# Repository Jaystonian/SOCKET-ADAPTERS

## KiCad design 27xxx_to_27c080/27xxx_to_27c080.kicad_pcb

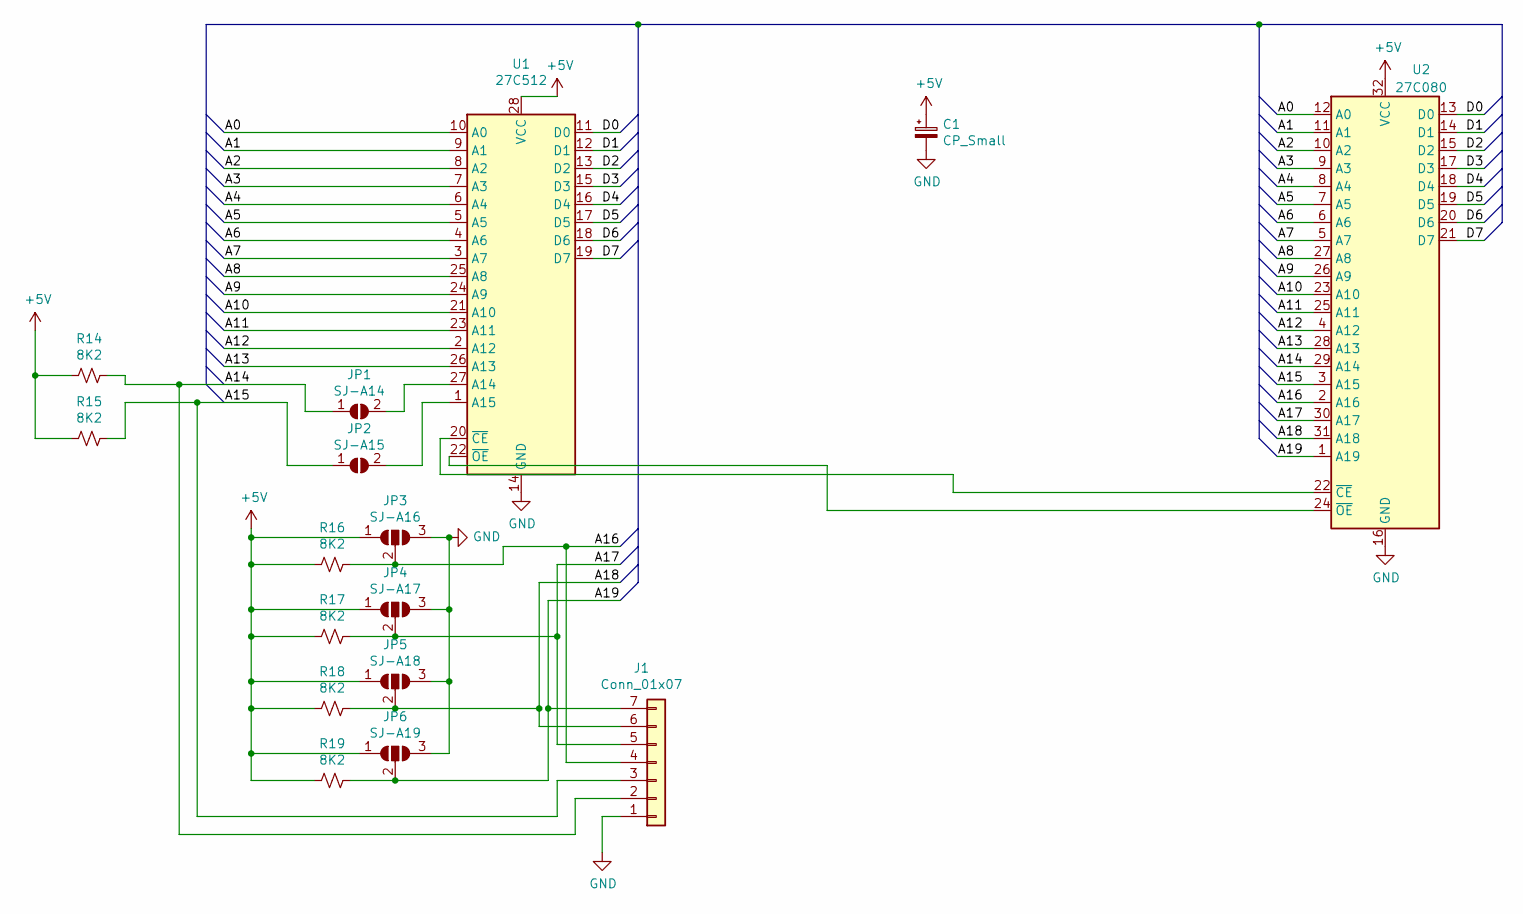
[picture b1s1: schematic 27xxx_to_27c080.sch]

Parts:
C1: CP_Small; CP_EIA-6032-28_Kemet-C_Pad2.25x2.35mm_HandSolder
J1: Conn_01x07; PinHeader_1x07_P2.54mm_Vertical
JP1: SJ-A14; SolderJumper-2_P1.3mm_Open_RoundedPad1.0x1.5mm
JP2: SJ-A15; SolderJumper-2_P1.3mm_Open_RoundedPad1.0x1.5mm
JP3: SJ-A16; SolderJumper-3_P1.3mm_Open_RoundedPad1.0x1.5mm_NumberLabels
JP4: SJ-A17; SolderJumper-3_P1.3mm_Open_RoundedPad1.0x1.5mm_NumberLabels
JP5: SJ-A18; SolderJumper-3_P1.3mm_Open_RoundedPad1.0x1.5mm_NumberLabels
JP6: SJ-A19; SolderJumper-3_P1.3mm_Open_RoundedPad1.0x1.5mm_NumberLabels
R14, R15, R16, R17, R18, R19: 8K2; R_0805_2012Metric_Pad1.15x1.40mm_HandSolder
U1: 27C512; DIP-28_W15.24mm
U2: 27C080; DIP-32_W15.24mm

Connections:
+5V: C1.1, JP3.1 (A), JP4.1 (A), JP5.1 (A), JP6.1 (A), R14.2, R15.2, R16.2, R17.2, R18.2, R19.2, U1.28 (VCC), U2.32 (VCC)
/A0: U1.10 (A0), U2.12 (A0)
/A1: U1.9 (A1), U2.11 (A1)
/A2: U1.8 (A2), U2.10 (A2)
/A3: U1.7 (A3), U2.9 (A3)
/A4: U1.6 (A4), U2.8 (A4)
/A5: U1.5 (A5), U2.7 (A5)
/A6: U1.4 (A6), U2.6 (A6)
/A7: U1.3 (A7), U2.5 (A7)
/A8: U1.25 (A8), U2.27 (A8)
/A9: U1.24 (A9), U2.26 (A9)
/A10: U1.21 (A10), U2.23 (A10)
/A11: U1.23 (A11), U2.25 (A11)
/A12: U1.2 (A12), U2.4 (A12)
/A13: U1.26 (A13), U2.28 (A13)
/A14: J1.2, JP1.1 (A), R14.1, U2.29 (A14)
/A15: J1.3, JP2.1 (A), R15.1, U2.3 (A15)
/A16: J1.4, JP3.2 (C), R16.1, U2.2 (A16)
/A17: J1.5, JP4.2 (C), R17.1, U2.30 (A17)
/A18: J1.6, JP5.2 (C), R18.1, U2.31 (A18)
/A19: J1.7, JP6.2 (C), R19.1, U2.1 (A19)
/D0: U1.11 (D0), U2.13 (D0)
/D1: U1.12 (D1), U2.14 (D1)
/D2: U1.13 (D2), U2.15 (D2)
/D3: U1.15 (D3), U2.17 (D3)
/D4: U1.16 (D4), U2.18 (D4)
/D5: U1.17 (D5), U2.19 (D5)
/D6: U1.18 (D6), U2.20 (D6)
/D7: U1.19 (D7), U2.21 (D7)
GND: C1.2, J1.1, JP3.3 (B), JP4.3 (B), JP5.3 (B), JP6.3 (B), U1.14 (GND), U2.16 (GND)
unnamed: JP1.2 (B), U1.27 (A14)
unnamed: JP2.2 (B), U1.1 (A15)
unnamed: U1.20 (~CE), U2.22 (~CE)
unnamed: U1.22 (~OE), U2.24 (~OE)

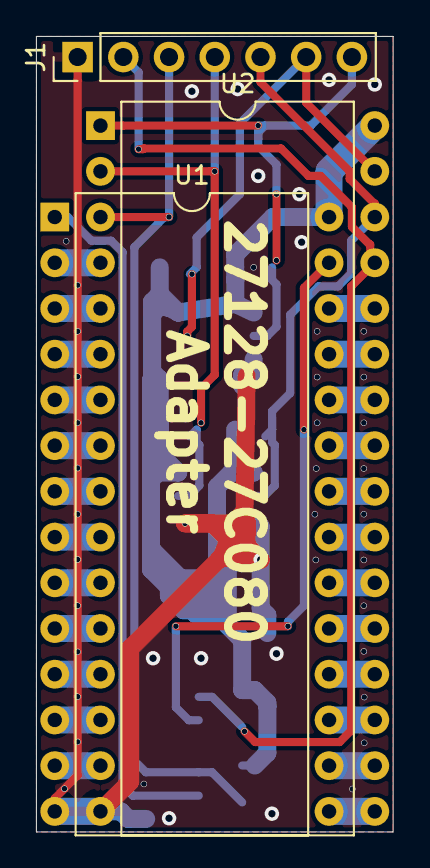
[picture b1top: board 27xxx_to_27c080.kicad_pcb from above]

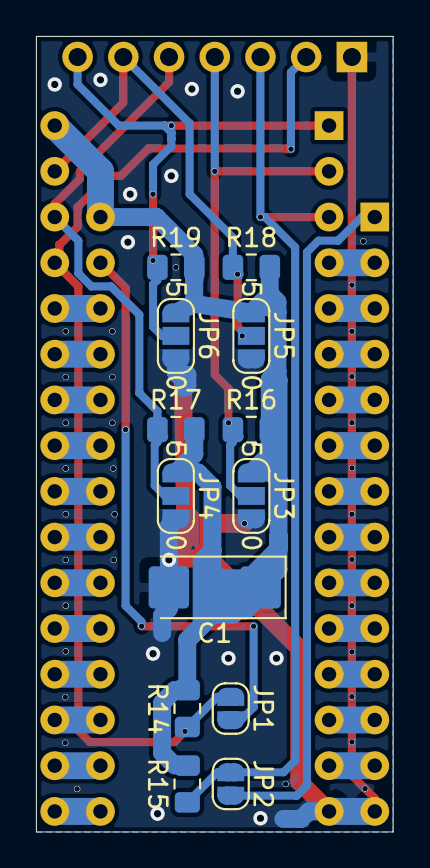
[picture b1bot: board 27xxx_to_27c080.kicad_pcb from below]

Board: 2 copper layers, 19.8 x 44.2 mm, 16 parts (13 on the bottom side), 34 nets.

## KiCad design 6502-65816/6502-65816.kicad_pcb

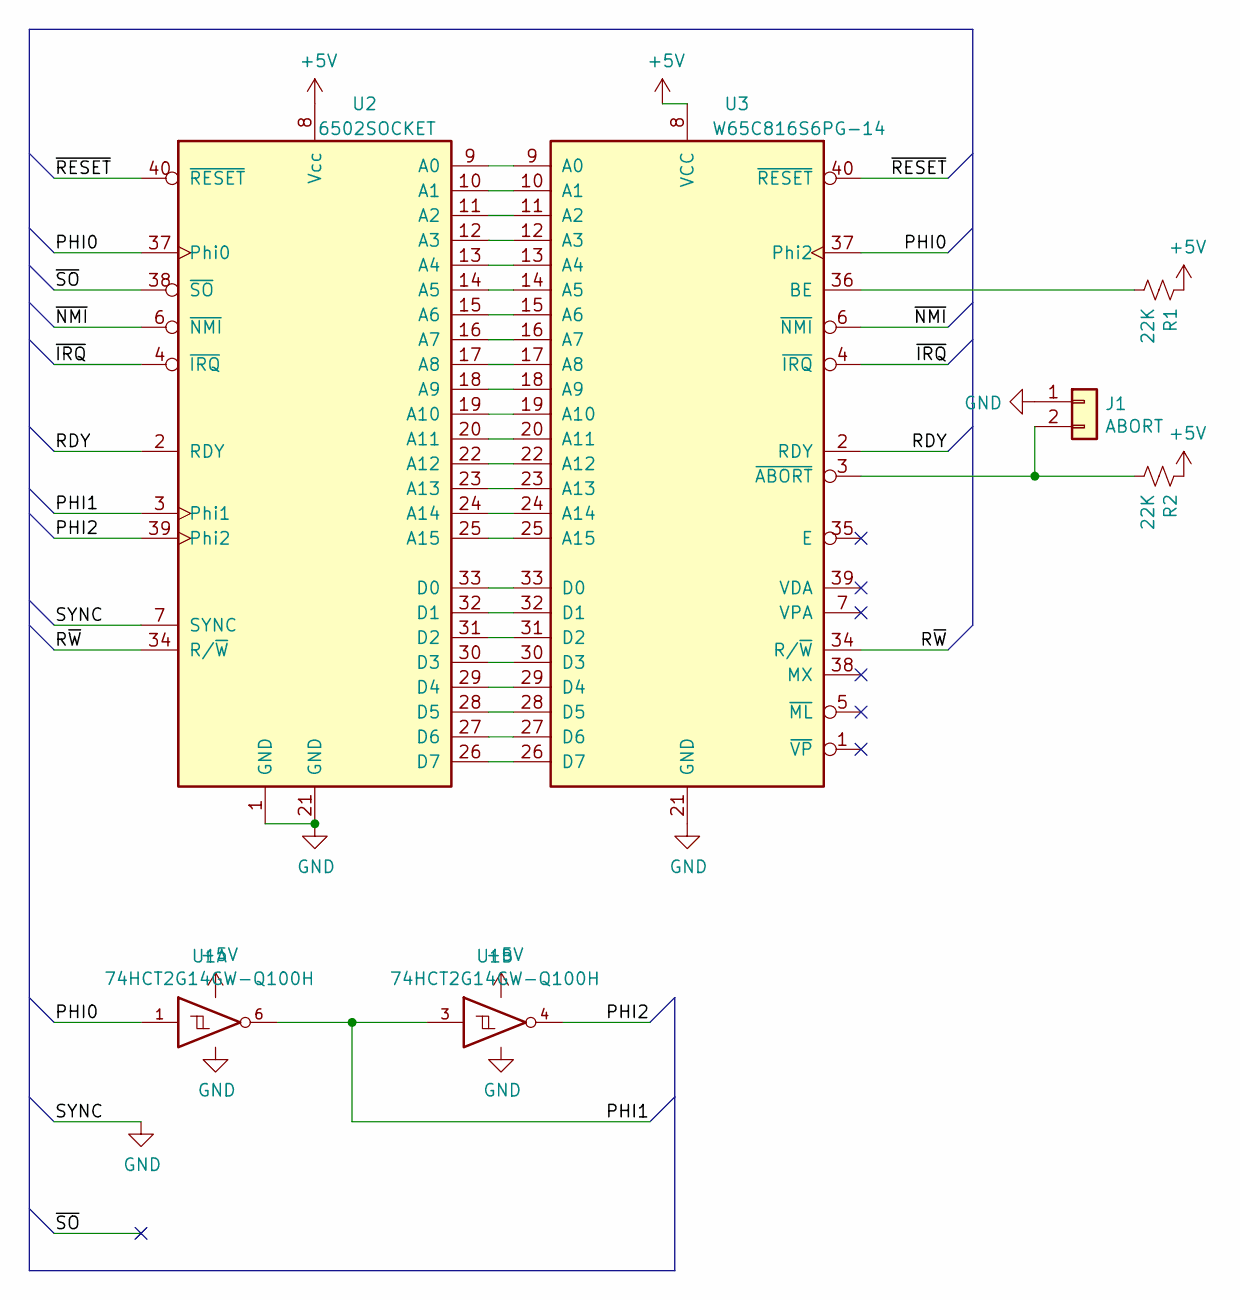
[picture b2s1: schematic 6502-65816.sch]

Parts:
J1: ABORT; PinHeader_1x02_P2.54mm_Vertical
R1, R2: 22K; R_0805_2012Metric_Pad1.15x1.40mm_HandSolder
U1: 74HCT2G14GW-Q100H; TSOP-6_1.65x3.05mm_P0.95mm
U2: 6502SOCKET; 6502CPU
U3: W65C816S6PG-14; W65C816CPU

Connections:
+5V: R1.1, R2.1, U1.5 (VCC), U2.8 (Vcc), U3.8 (VCC)
/PHI0: U1.1, U2.37 (Phi0), U3.37 (Phi2)
/PHI1: U1.3, U1.6, U2.3 (Phi1)
/PHI2: U1.4, U2.39 (Phi2)
/RDY: U2.2 (RDY), U3.2 (RDY)
/R~W: U2.34 (R/~W~), U3.34 (R/~W~)
/~IRQ: U2.4 (~IRQ~), U3.4 (~IRQ~)
/~NMI: U2.6 (~NMI~), U3.6 (~NMI~)
/~RESET: U2.40 (~RESET~), U3.40 (~RESET~)
/~SO: U2.38 (~SO~)
GND: J1.1, U1.2 (GND), U2.1 (GND), U2.7 (SYNC), U2.21 (GND), U3.21 (GND)
unnamed: J1.2, R2.2, U3.3 (~ABORT~)
unnamed: R1.2, U3.36 (BE)
unnamed: U2.9 (A0), U3.9 (A0)
unnamed: U2.10 (A1), U3.10 (A1)
unnamed: U2.11 (A2), U3.11 (A2)
unnamed: U2.12 (A3), U3.12 (A3)
unnamed: U2.13 (A4), U3.13 (A4)
unnamed: U2.14 (A5), U3.14 (A5)
unnamed: U2.15 (A6), U3.15 (A6)
unnamed: U2.16 (A7), U3.16 (A7)
unnamed: U2.17 (A8), U3.17 (A8)
unnamed: U2.18 (A9), U3.18 (A9)
unnamed: U2.19 (A10), U3.19 (A10)
unnamed: U2.20 (A11), U3.20 (A11)
unnamed: U2.22 (A12), U3.22 (A12)
unnamed: U2.23 (A13), U3.23 (A13)
unnamed: U2.24 (A14), U3.24 (A14)
unnamed: U2.25 (A15), U3.25 (A15)
unnamed: U2.26 (D7), U3.26 (D7)
unnamed: U2.27 (D6), U3.27 (D6)
unnamed: U2.28 (D5), U3.28 (D5)
unnamed: U2.29 (D4), U3.29 (D4)
unnamed: U2.30 (D3), U3.30 (D3)
unnamed: U2.31 (D2), U3.31 (D2)
unnamed: U2.32 (D1), U3.32 (D1)
unnamed: U2.33 (D0), U3.33 (D0)

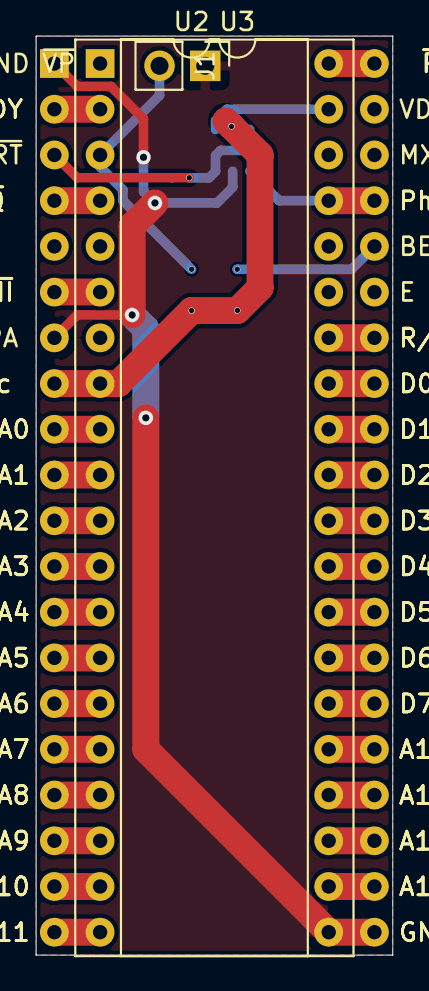
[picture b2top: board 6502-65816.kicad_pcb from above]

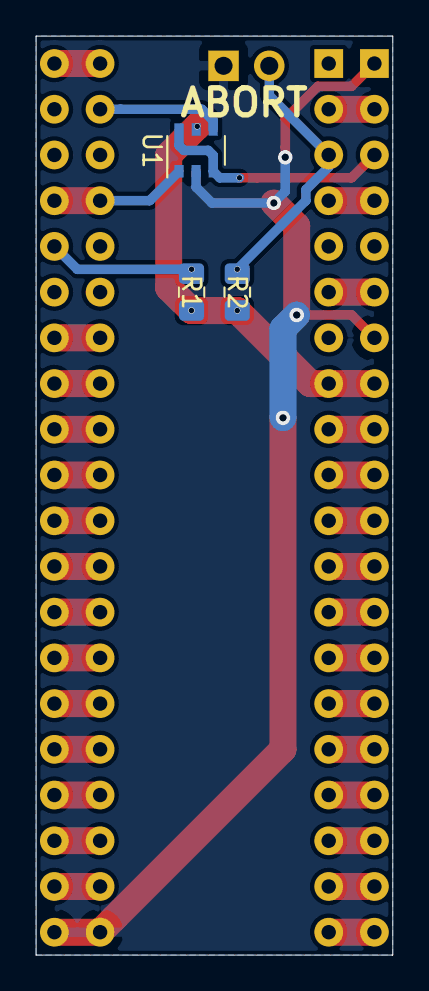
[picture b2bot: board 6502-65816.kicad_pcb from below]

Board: 2 copper layers, 19.8 x 51.1 mm, 6 parts (3 on the bottom side), 36 nets.

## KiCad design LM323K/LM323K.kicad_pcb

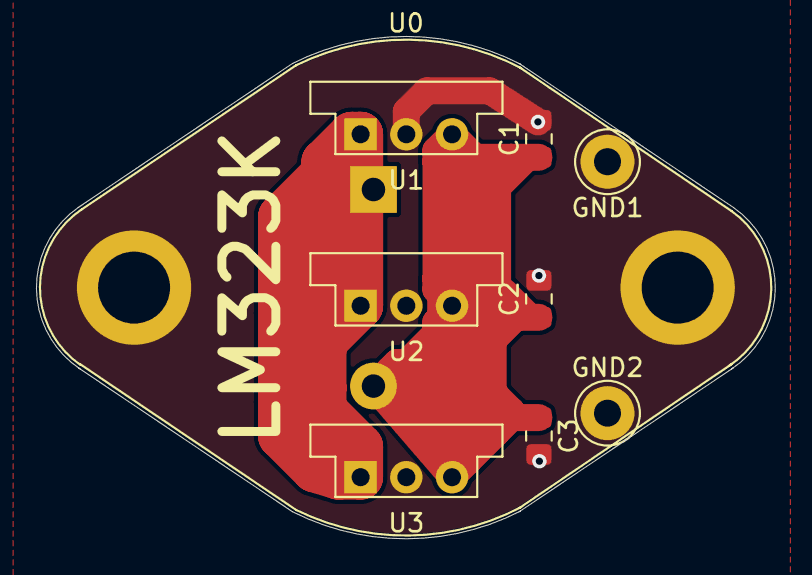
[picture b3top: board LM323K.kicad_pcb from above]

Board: 2 copper layers, 41.0 x 27.9 mm, 9 parts (0 on the bottom side), 3 nets.

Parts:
C1, C2, C3: C_Small; C_0805_2012Metric_Pad1.15x1.40mm_HandSolder
GND1, GND2: Conn_01x01; Pin_D1.3mm_L11.0mm_LooseFit
U0: LM323K; TO-3
U1: 78SR; Converter_DCDC_muRata_OKI-78SR_Vertical
U2, U3: L7805; Converter_DCDC_muRata_OKI-78SR_Vertical

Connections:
GND: C1.2, C2.2, C3.2, GND1.1, GND2.1, U0.3, U1.2, U2.2, U3.2
unnamed: C1.1, C2.1, C3.1, U0.2, U1.3, U2.3, U3.3
unnamed: U0.1, U1.1, U2.1, U3.1

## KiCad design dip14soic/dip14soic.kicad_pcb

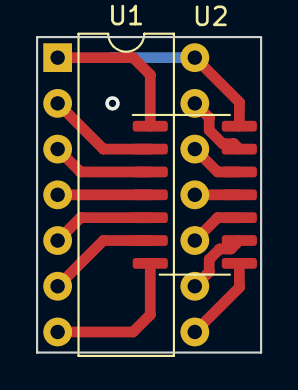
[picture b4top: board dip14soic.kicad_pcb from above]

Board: 2 copper layers, 12.4 x 17.5 mm, 3 parts (1 on the bottom side), 14 nets.

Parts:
C1: 100n; C_0805_2012Metric_Pad1.15x1.40mm_HandSolder
U1: 74LS00; DIP-14_W7.62mm
U2: 74LS00; SOIC-14_3.9x8.7mm_P1.27mm

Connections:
unnamed: C1.1, U1.14, U2.14
unnamed: C1.2, U1.7, U2.7
unnamed: U1.1, U2.1
unnamed: U1.2, U2.2
unnamed: U1.3, U2.3
unnamed: U1.4, U2.4
unnamed: U1.5, U2.5
unnamed: U1.6, U2.6
unnamed: U1.8, U2.8
unnamed: U1.9, U2.9
unnamed: U1.10, U2.10
unnamed: U1.11, U2.11
unnamed: U1.12, U2.12
unnamed: U1.13, U2.13
